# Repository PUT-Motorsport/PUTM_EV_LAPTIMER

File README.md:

# PUTM EV LAPTIMER

## About
This is standalone laptimer for Formula Student made on ESP32-S3 with ESP-IDF and LVGL. It provides simple way to monitor your lap times during trainings and vehicle tests.

## Features
- Measure lap time using one or two measure gates
- Save lap times on SD card
- Watch lap times on LCD or webpage
- Download .csv files with sorted lap times
- Add penalties from FSG Rules during laptime

## How to use
LCD GUI:
<br/>

1. SD card status
   - RED - not initialized
   - GREEN - initialized
2. WIFI status, mode and IP
   - RED - not initialized
   - GREEN - initialized
   - STA - station mode
   -  AP - access point mode
3. Gate mode
   - 1 GATE - like F1 race finish line, next lap starts automatically 
   - 2 GATES - one gate starts lap, second gate ends lap, then timer stops
4. RUN/STOP
   - RED - lap stopped
   - GREEN - lap in progress
5. Current lap time
6. Current lap info
   - DRIVER - tag of current driver
   - LAP - lap count
   - OC - number of FSG OC penalties
   - DOO - number of FSG DOO penalties
   - PENALTY - cumulated penalty time added to current lap time after finishing
7. Lap time lists
   <br/>
Similar interface can be accessed by connecting to a webpage hosted on ip address displayed on LCD. Moreover, on webpage you can download .csv files with lap times and change system configuration settings:
- Gate mode
- Wifi mode
- SSID and password of wifi network
- Date and time
- List of drivers
Those settings can be also changed by inserting SD card with [config file](firmware/main/config.txt)<br/>
## How to install
1. It's recommended to install ESP-IDF for Visual Studio Code with [this guide](https://github.com/espressif/vscode-esp-idf-extension/blob/master/README.md).
2. After cloning repository you should configure ESP-IDF project using
```
idf.py menuconfig
```
in CLI with activated ESP-IDF or 
```
>ESP-IDF: SDK Configuration Editor (Menuconfig)
```
in VSCode Command Palette, pin assignment and some other settings can be set in (Component config)/(PUTM EV Laptimer).
Default pin assignment is for ESP32-S3 and matches shield hardware used in this project.
<br/><br/>
3. Run
```
idf.py build
```
in CLI or
```
>ESP-IDF: Build Your Project
```
in Command Palette to build project
4. Easy way to quickly rebuild and flash project is to use command
```
>ESP-IDF: Build, Flash and Start a Monitor on Your Device
```
also available from VSCode status bar. You will also see program output in CLI. 
<br/>

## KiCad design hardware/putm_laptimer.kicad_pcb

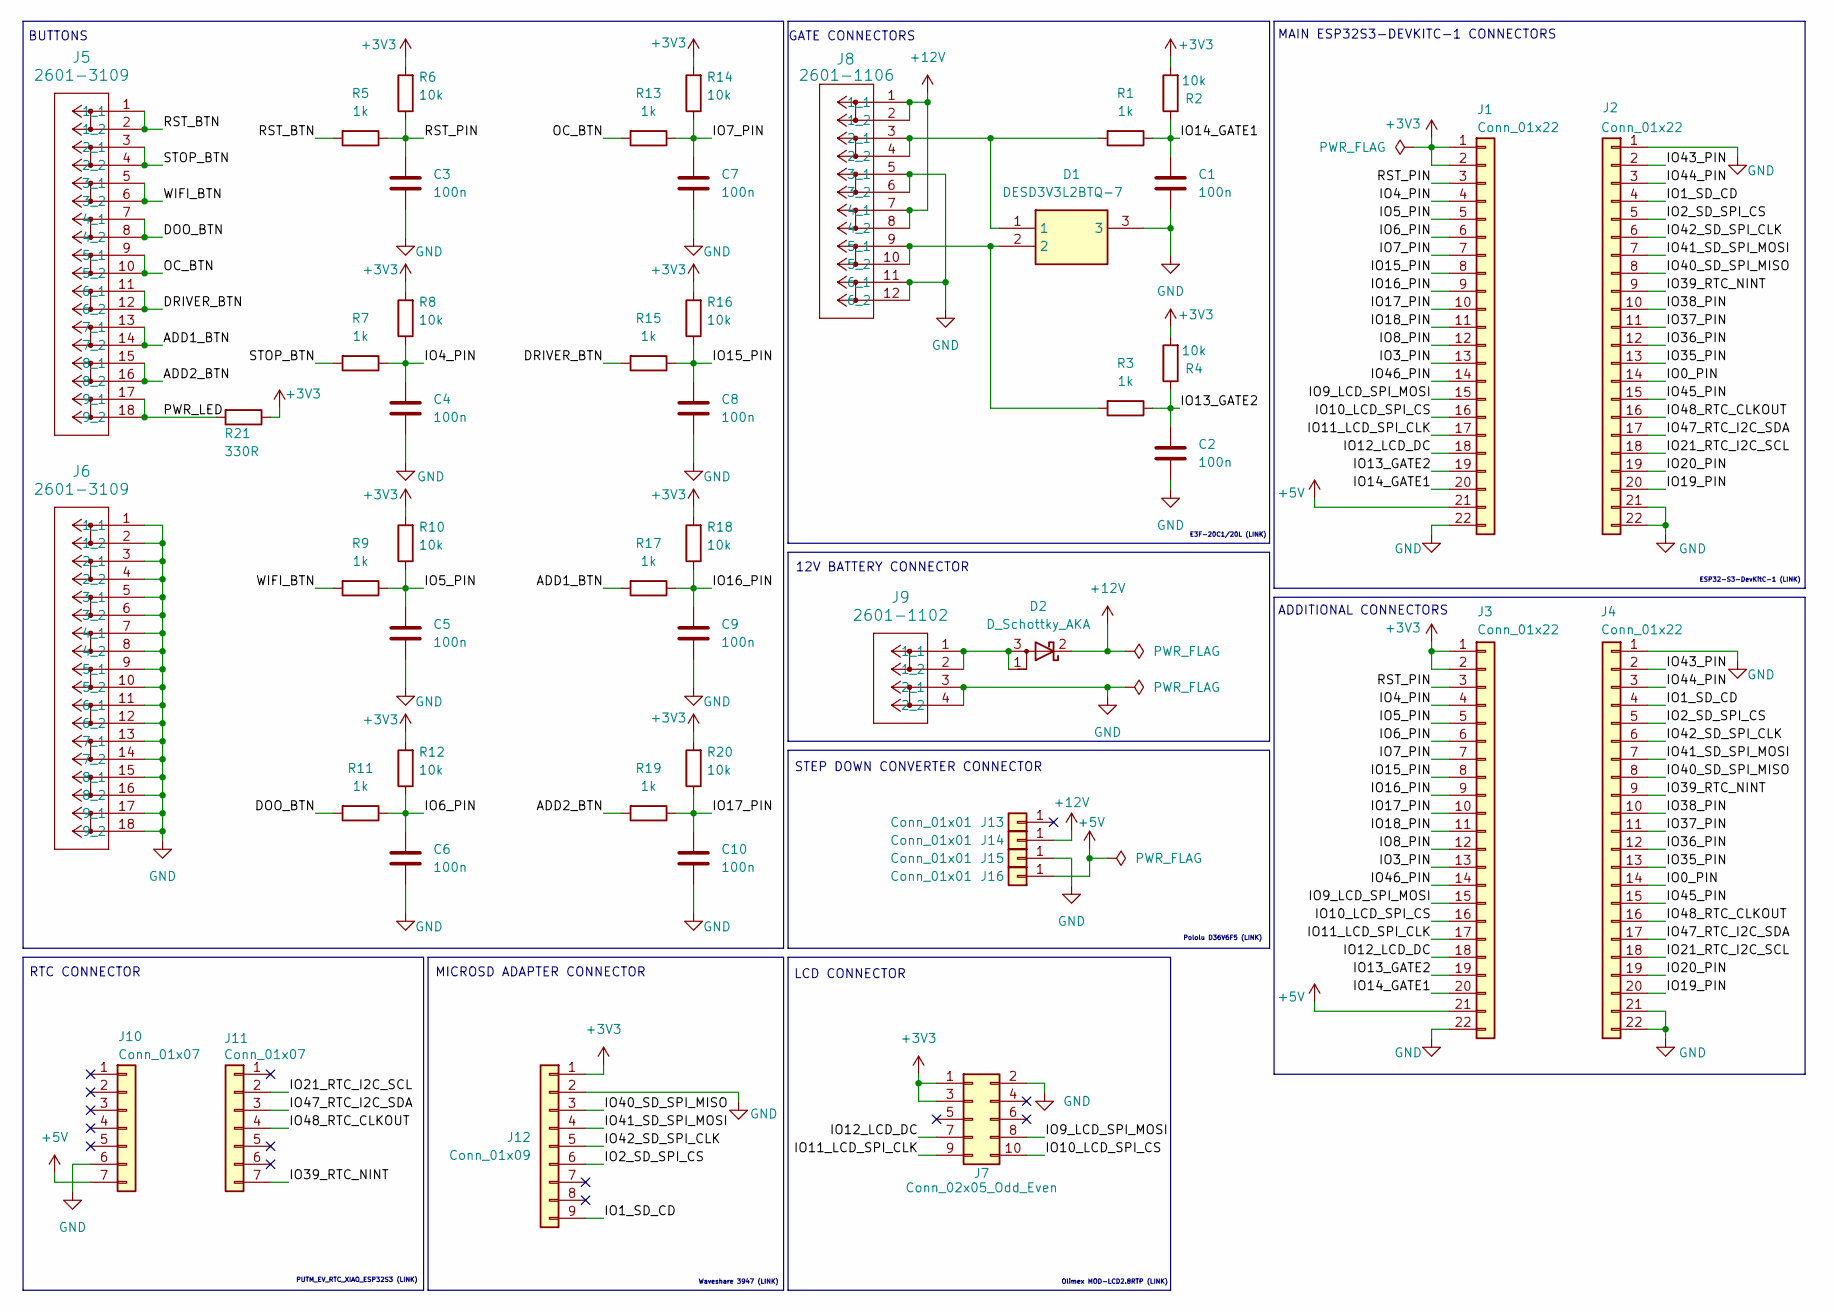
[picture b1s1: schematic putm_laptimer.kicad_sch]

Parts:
C1, C2, C3, C4, C5, C6, C7, C8, C9, C10: 100n; C_0603_1608Metric; Manufacturer_Part_Number GRM033R6YA104ME14D; Mouser/TME part number 81-GRM33R6YA104ME14D
D1: DESD3V3L2BTQ-7; SOT96P240X110-3N; Manufacturer_Part_Number DESD3V3L2BTQ-7; Mouser/TME part number 621-DESD3V3L2BTQ-7
D2: D_Schottky_AKA; VS50WQ03FNM3; Mouser/TME part number 844-50WQ03FN-M3
J1, J2, J3, J4: Conn_01x22; PinSocket_1x22_P2.54mm_Vertical; Manufacturer_Part_Number DS1023-1*40S21; Mouser/TME part number ZL262-40SG
J5, J6: 2601-3109; CONN9_2601-3109_WAG; Manufacturer_Part_Number 2601-3109; Mouser/TME part number sample
J7: Conn_02x05_Odd_Even; PinHeader_2x05_P2.54mm_Vertical; Manufacturer_Part_Number DS1013-10SSIB1-B-0; Mouser/TME part number ZL231-10PG
J8: 2601-1106; CONN6_2601-1106_WAG; Manufacturer_Part_Number 2601-1106; Mouser/TME part number sample
J9: 2601-1102; CONN2_2601-1102_WAG; Manufacturer_Part_Number 2601-1102; Mouser/TME part number sample
J10, J11: Conn_01x07; PinSocket_1x07_P2.54mm_Vertical; Manufacturer_Part_Number DS1023-1*7S21; Mouser/TME part number ZL262-7SG
J12: Conn_01x09; PinSocket_1x09_P2.54mm_Horizontal; Manufacturer_Part_Number DS1023-1*9S21; Mouser/TME part number ZL262-9SG
J13, J14, J15, J16: Conn_01x01; TestPoint_THTPad_D2.0mm_Drill1.0mm
R1, R3, R5, R7, R9, R11, R13, R15, R17, R19: 1k; R_0603_1608Metric; Manufacturer_Part_Number CR0603-FX-1001ELF; Mouser/TME part number 652-CR0603FX-1001ELF
R2, R4, R6, R8, R10, R12, R14, R16, R18, R20: 10k; R_0603_1608Metric; Manufacturer_Part_Number CR0603-FX-1002ELF; Mouser/TME part number 652-CR0603FX-1002ELF
R21: 330R; R_0603_1608Metric; Manufacturer_Part_Number CR0603-FX-3300ELF; Mouser/TME part number 652-CR0603FX-3300ELF

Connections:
+3V3: J1.1, J1.2, J3.1, J3.2, J7.1, J7.3, J12.1, R2.2, R4.2, R6.2, R8.2, R10.2, R12.2, R14.2, R16.2, R18.2, R20.2, R21.1
+5V: J1.21, J3.21, J10.7, J16.1
+12V: D2.2 (K), J8.1 (1_1), J8.2 (1_2), J8.7 (4_1), J8.8 (4_2), J14.1
/ADD1_BTN: J5.13 (7_1), J5.14 (7_2), R17.2
/ADD2_BTN: J5.15 (8_1), J5.16 (8_2), R19.2
/DOO_BTN: J5.7 (4_1), J5.8 (4_2), R11.2
/DRIVER_BTN: J5.11 (6_1), J5.12 (6_2), R15.2
/IO0_PIN: J2.14, J4.14
/IO1_SD_CD: J2.4, J4.4, J12.9
/IO2_SD_SPI_CS: J2.5, J4.5, J12.6
/IO3_PIN: J1.13, J3.13
/IO4_PIN: C4.1, J1.4, J3.4, R7.1, R8.1
/IO5_PIN: C5.1, J1.5, J3.5, R9.1, R10.1
/IO6_PIN: C6.1, J1.6, J3.6, R11.1, R12.1
/IO7_PIN: C7.1, J1.7, J3.7, R13.1, R14.1
/IO8_PIN: J1.12, J3.12
/IO9_LCD_SPI_MOSI: J1.15, J3.15, J7.8
/IO10_LCD_SPI_CS: J1.16, J3.16, J7.10
/IO11_LCD_SPI_CLK: J1.17, J3.17, J7.9
/IO12_LCD_DC: J1.18, J3.18, J7.7
/IO13_GATE2: C2.1, J1.19, J3.19, R3.1, R4.1
/IO14_GATE1: C1.1, J1.20, J3.20, R1.1, R2.1
/IO15_PIN: C8.1, J1.8, J3.8, R15.1, R16.1
/IO16_PIN: C9.1, J1.9, J3.9, R17.1, R18.1
/IO17_PIN: C10.1, J1.10, J3.10, R19.1, R20.1
/IO18_PIN: J1.11, J3.11
/IO19_PIN: J2.20, J4.20
/IO20_PIN: J2.19, J4.19
/IO21_RTC_I2C_SCL: J2.18, J4.18, J11.2
/IO35_PIN: J2.13, J4.13
/IO36_PIN: J2.12, J4.12
/IO37_PIN: J2.11, J4.11
/IO38_PIN: J2.10, J4.10
/IO39_RTC_NINT: J2.9, J4.9, J11.7
/IO40_SD_SPI_MISO: J2.8, J4.8, J12.3
/IO41_SD_SPI_MOSI: J2.7, J4.7, J12.4
/IO42_SD_SPI_CLK: J2.6, J4.6, J12.5
/IO43_PIN: J2.2, J4.2
/IO44_PIN: J2.3, J4.3
/IO45_PIN: J2.15, J4.15
/IO46_PIN: J1.14, J3.14
/IO47_RTC_I2C_SDA: J2.17, J4.17, J11.3
/IO48_RTC_CLKOUT: J2.16, J4.16, J11.4
/OC_BTN: J5.9 (5_1), J5.10 (5_2), R13.2
/PWR_LED: J5.17 (9_1), J5.18 (9_2), R21.2
/RST_BTN: J5.1 (1_1), J5.2 (1_2), R5.2
/RST_PIN: C3.1, J1.3, J3.3, R5.1, R6.1
/STOP_BTN: J5.3 (2_1), J5.4 (2_2), R7.2
/WIFI_BTN: J5.5 (3_1), J5.6 (3_2), R9.2
GND: C1.2, C2.2, C3.2, C4.2, C5.2, C6.2, C7.2, C8.2, C9.2, C10.2, D1.3, J1.22, J2.1, J2.21, J2.22, J3.22, J4.1, J4.21, J4.22, J6.1 (1_1), J6.2 (1_2), J6.3 (2_1), J6.4 (2_2), J6.5 (3_1), J6.6 (3_2), J6.7 (4_1), J6.8 (4_2), J6.9 (5_1), J6.10 (5_2), J6.11 (6_1), J6.12 (6_2), J6.13 (7_1), J6.14 (7_2), J6.15 (8_1), J6.16 (8_2), J6.17 (9_1), J6.18 (9_2), J7.2, J8.5 (3_1), J8.6 (3_2), J8.11 (6_1), J8.12 (6_2), J9.3 (2_1), J9.4 (2_2), J10.6, J12.2, J15.1
unnamed: D1.1, J8.3 (2_1), J8.4 (2_2), R1.2
unnamed: D1.2, J8.9 (5_1), J8.10 (5_2), R3.2
unnamed: D2.1 (A), D2.3 (A), J9.1 (1_1), J9.2 (1_2)

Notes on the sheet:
Waveshare 3947 (LINK)
E3F-20C1/20L (LINK)
12V BATTERY CONNECTOR
ADDITIONAL CONNECTORS
GATE CONNECTORS
MAIN ESP32S3-DEVKITC-1 CONNECTORS
Pololu D36V6F5 (LINK)
BUTTONS
STEP DOWN CONVERTER CONNECTOR
Olimex MOD-LCD2.8RTP (LINK)
PUTM_EV_RTC_XIAO_ESP32S3 (LINK)
MICROSD ADAPTER CONNECTOR
ESP32-S3-DevKitC-1 (LINK)
RTC CONNECTOR
LCD CONNECTOR

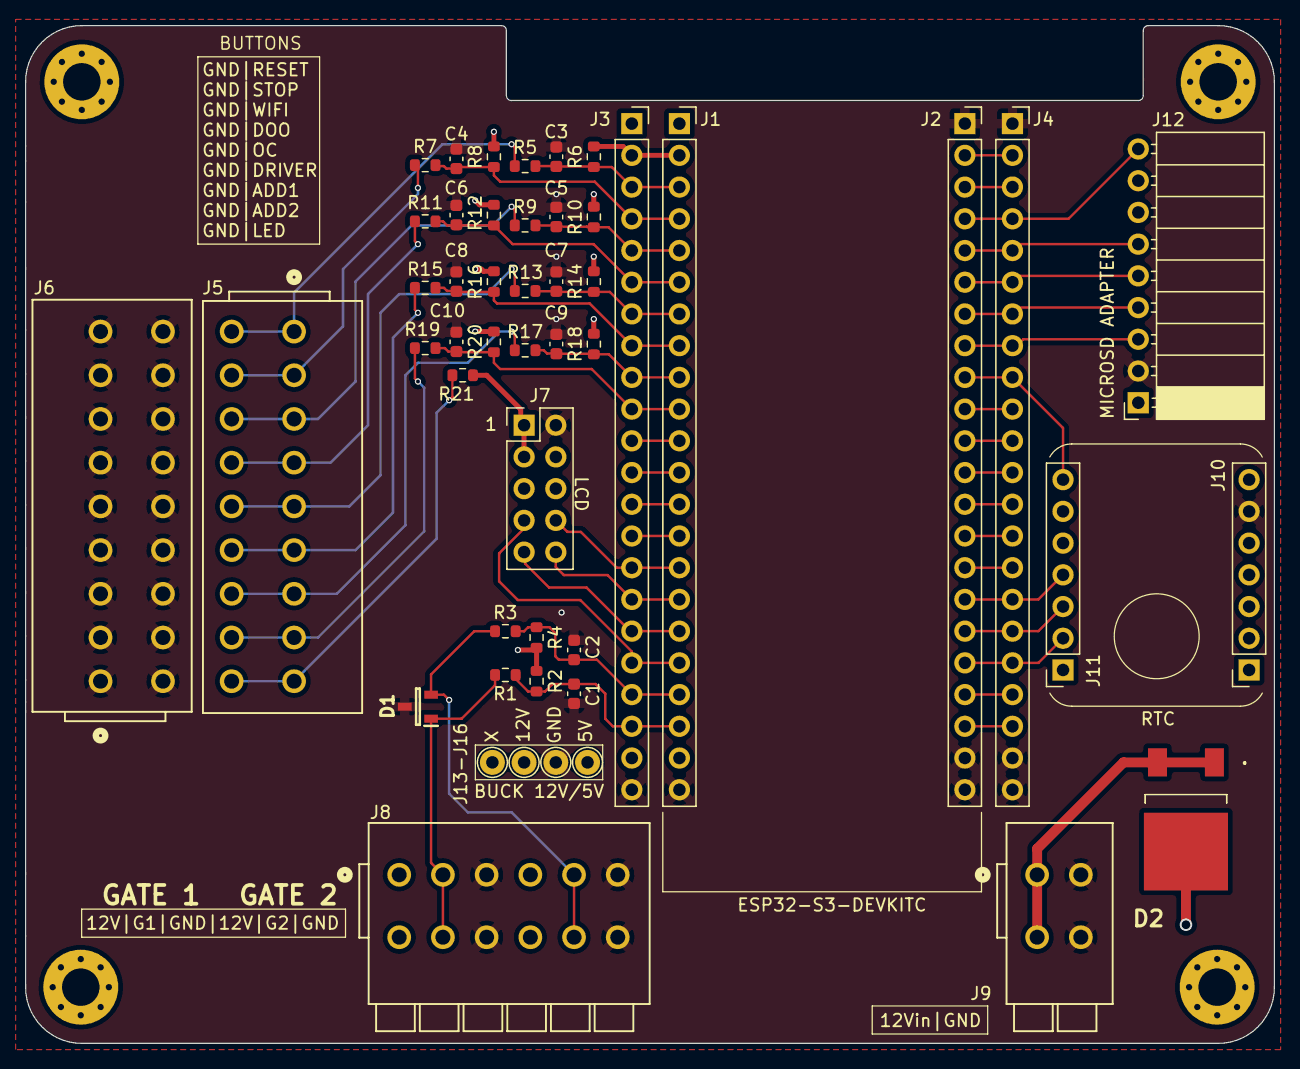
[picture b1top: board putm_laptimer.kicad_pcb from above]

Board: 4 copper layers, 100.0 x 81.5 mm, 49 parts (0 on the bottom side), 53 nets.

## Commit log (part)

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2025-11-26 fix hagl component
2025-11-26 fix includes and macros
2025-11-26 add program status display on lcd
2025-11-26 fix task priority
2025-11-27 modify hagl to use char instead of wchar_t, change laptime list queue to semaphore with global array
2025-11-27 fix font buffer issue
2025-11-27 update gitignore
2025-11-30 - added wifi ap task that creates website providing same info as lcd
2025-11-30 - changed lcd gui elements positions - fixed sdcard spi dma initialization bug
2025-12-01 added tasks documentation
2025-12-01 fixed sdcard save format
2025-12-02 fixed sdcard reinitialization bug
2025-12-02 added checking if laptime saved properly on sdcard
2025-12-03 - added defines for status flags - added better documentation for laptime lists
2025-12-03 fixed sdcard save check bug
2025-12-03 added working buttons for adding/deleting time penalties from fsg rules
2025-12-03 updated exisitng laptime structures to be able to pass penalty time to other tasks
2025-12-03 converted Laptime struct into class
2025-12-05 changed laptime_save_local
2025-12-05 working current penalty display on lcd
2025-12-05 working doo and oc count display on lcd
2025-12-07 updated pinout for esp32s3 and added pinout configuration through kconfig
2025-12-07 added penalty display on webpage
2025-12-07 added download csv button to website
2025-12-08 fixed status flags bug
2025-12-09 updated sdcard speed
2025-12-09 sdcard now uses card detect pin on new adapter that allows to easier initialize and deinitialize
2025-12-10 added button for switching drivers, changed button hold logic
2025-12-10 added current driver display on lcd
2025-12-10 added laptime lists driver tag color display on lcd
2025-12-12 added drivers display on webpage
2025-12-12 added drivers on website with best laptimes and sum of penalties
2025-12-14 updated sdkconfig for esp32s3
2025-12-14 updated communication between tasks
2025-12-14 updated sdcard save format to save laptime penalties and drivers
2025-12-14 added reading driver list from sdcard
2025-12-15 fixed sdcard driver list reading bug, added local driver lists in tasks
2025-12-15 fixed wifi webpage bug
2025-12-17 added sd_cd gpio config
2025-12-17 added internal pull down for reset btn
2025-12-21 - fixed pinout - created structure for config - added station mode to wifi
2025-12-21 deleted lap mode button and added wifi reset button
2025-12-21 added wifi reinitialization function
2025-12-22 tidy up code
2025-12-22 added wifi reset to safe values on button long press
2025-12-22 moved webpage html to separete file
2025-12-22 added mdns for wifi station
2025-12-23 added config load from sdcard and wifi webpage
2025-12-25 added date and time of day assigned to laptime
2025-12-25 added function to modify system time
2025-12-26 added ip address display on lcd
2025-12-27 added wifi mode display on lcd
2025-12-28 added date column to .csv
2025-12-28 added system time and date set on webpage
2025-12-28 reduced spi speed
2026-01-12 added schematics and pcb prototype
2026-01-12 added pcb files
2026-01-12 changed pinout to match pcb
2026-01-15 deleted buttons on board and added hawrin connector
2026-01-15 gitignore fix
2026-01-15 gitignore update
2026-01-15 config update
2026-01-17 added rtc connectors to schematics
2026-01-18 placed rtc connectors on pcb
2026-01-18 changed harwin connector to connect power led, updated cleareance and net width
2026-01-18 updated pinout config to match kicad schematics
2026-01-18 update isr time read to increase accuracy
2026-01-18 added documentation for task loops
2026-01-18 updated Kconfig
2026-01-18 added arduino component
2026-01-18 imported RV3028 rtc arduino library
2026-01-18 added init function for rtc
2026-01-19 changed element placement
2026-01-19 changed time and date format to match iso8601 used by rv3028c7 rtc
2026-01-19 added functions to set/get time and date from external RV3028 rtc
2026-01-19 fixed config
2026-01-19 fixed rtc error
2026-01-20 fixed webpage config bug
2026-01-25 Added connectors for step-up converter and changed wago connectors to 6-pin
2026-01-26 Changed layout
2026-01-26 Fixed connector footprint
2026-01-26 Fixed footprint refrence on silkscreen
2026-01-26 Added board dimensions
2026-01-31 Fixed borders
2026-01-31 Added modules info and links to connector schematics
2026-02-01 Fixed routing
2026-02-02 Changed layout, changed gate connector, added 12V battery connector and buck converter pins
2026-02-02 Fixed schematics
2026-02-03 Fixed pcb layout
2026-02-03 Changed .gitigone
2026-02-04 Increased buck converter pin hole diameter
2026-02-04 Changed connectors
2026-02-06 Added pwr flags on battery connector and fixed wago connector footprint malformed courtyard
2026-02-06 Added reverse polarity protection diode, deleted unused footprints
2026-02-08 Changed esp32 connector
2026-02-08 Added part numbers
2026-02-08 Fixed silkscreen text size
2026-02-09 Fixed connector placing
2026-02-09 Fixed silkscreen text
2026-02-09 Fixed trace routing
2026-02-11 Edit pcb
2026-02-11 Fixed wago connector place, resized board
2026-02-11 Changed lcd connector model
2026-02-11 Changed pull up ressistor trace
2026-02-11 Fixed silkscreen
2026-02-11 Sync
2026-02-12 Changed capactitor model
2026-02-12 Changed buck converter position
2026-02-12 Fixed silkscreen overlap
2026-02-12 Merge
2026-02-12 Fixed memory copy error
2026-02-12 Simplified status flags
2026-02-12 Fixed sdcard init bug
2026-02-12 Added creating default config file on sd card when inserting first time
2026-02-12 Changed fatfs config to read .json file
2026-02-14 Simplified wifi reset and initialization process
2026-02-14 Fixed bom table
2026-02-15 Added function documentation
2026-02-19 Table part numbers fix
2026-02-19 Added second gate connector
2026-02-20 Trying to fix
2026-02-20 working lvgl
2026-02-22 Fixed lcd flickering issue, added status update on lcd
2026-02-22 New status icons:
2026-02-26 Updated gui
2026-02-27 Fixed ip display bug on lcd
2026-02-27 Fixed laptime lists refresh bug
2026-02-27 Added better monospaced fonts
2026-02-27 Changed lcd layout
2026-02-27 Changed gui look
2026-02-27 New GUI
2026-02-28 Fixed laptime to string conversion
2026-02-28 Fixed ip queue
2026-02-28 Added wireless two gate mode configuration
2026-03-01 Added better main.h documentation
2026-03-02 Fixed types
2026-03-02 Fixed includes
2026-03-03 Added better lcd refresh system
2026-03-03 Fixed date format
2026-03-03 Removed runtime reinitialization of wifi driver
2026-03-03 Better webserver initializtation, wifi driver fixes
2026-03-03 Added esp32 compatibility through kconfig
2026-03-04 Added new file with defines
2026-03-05 Fixed laptime lists display on lcd
2026-03-09 Fixed lcd bug
2026-03-13 Changed reverse polarity protection schottky diode
2026-03-13 Changed silkscreen info tables
2026-03-13 Revise README
    Updated project information and installation instructions for the PUTM EV Laptimer.
2026-03-13 Added gui jpg for documentation
2026-03-14 Enhance README with LCD GUI and installation details
    Added detailed LCD GUI usage instructions and configuration options.
2026-03-16 Added docs for new schottky
2026-03-18 minor fixes
2026-03-20 Added sign on silkscreen
2026-04-14 updated to kicad 10, fixed buck converter marking error, slightly moved elements near LCD 2x5 connector
2026-04-22 replaced cjson with arduinojson
2026-04-23 fixed: driver list update bug, sd card reinitialization bug
